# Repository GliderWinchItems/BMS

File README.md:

# BMS
Battery Management System

This repo has directories for three BMS designs.

The original plan used a LTC6813-1 (18 cells), but when it came time to order the pcb, the part was no longer available. The TI BQ76952 (16 cells) was then found to be available in a few months so that design was completed.
The testing of the first prototype with the BQA76952 turned up some unexplained failures, plus additional BQ76952 parts would not be available for approximately one year. 

The ADBMS1818 chip became available and samples were to be shipped in a few weeks, and additional parts available from Mouser in several months. This gave rise to the second design. The delivery schedule changed  and it would be about one year for samples and additional parts. This gave rise to a design based on the MAX14952.
The designs differ mainly in the BMS chip. The same processor, STM32L431RxT6, is used and the features are  nearly identical in the three designs, e.g. the trickle charger, CAN, and fan interfaces, etc. Much of the documentation for the BQ76952 board applies to all three designs.

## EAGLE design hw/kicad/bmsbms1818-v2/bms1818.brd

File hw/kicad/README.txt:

#README.txt
# 11/08/25

# Step 1: Convert eagle v4 format to v6.5
#
# The files in kicad are the result of loading the original eagle v4 files into
# eagle 6.5, then saving the .sch & .brd files.

# Step 2: Convert eagle 6.5 format to kicad.
#
# The eagle 6.5 files are imported into kicad and the resulting kicad format files are 
# saved.

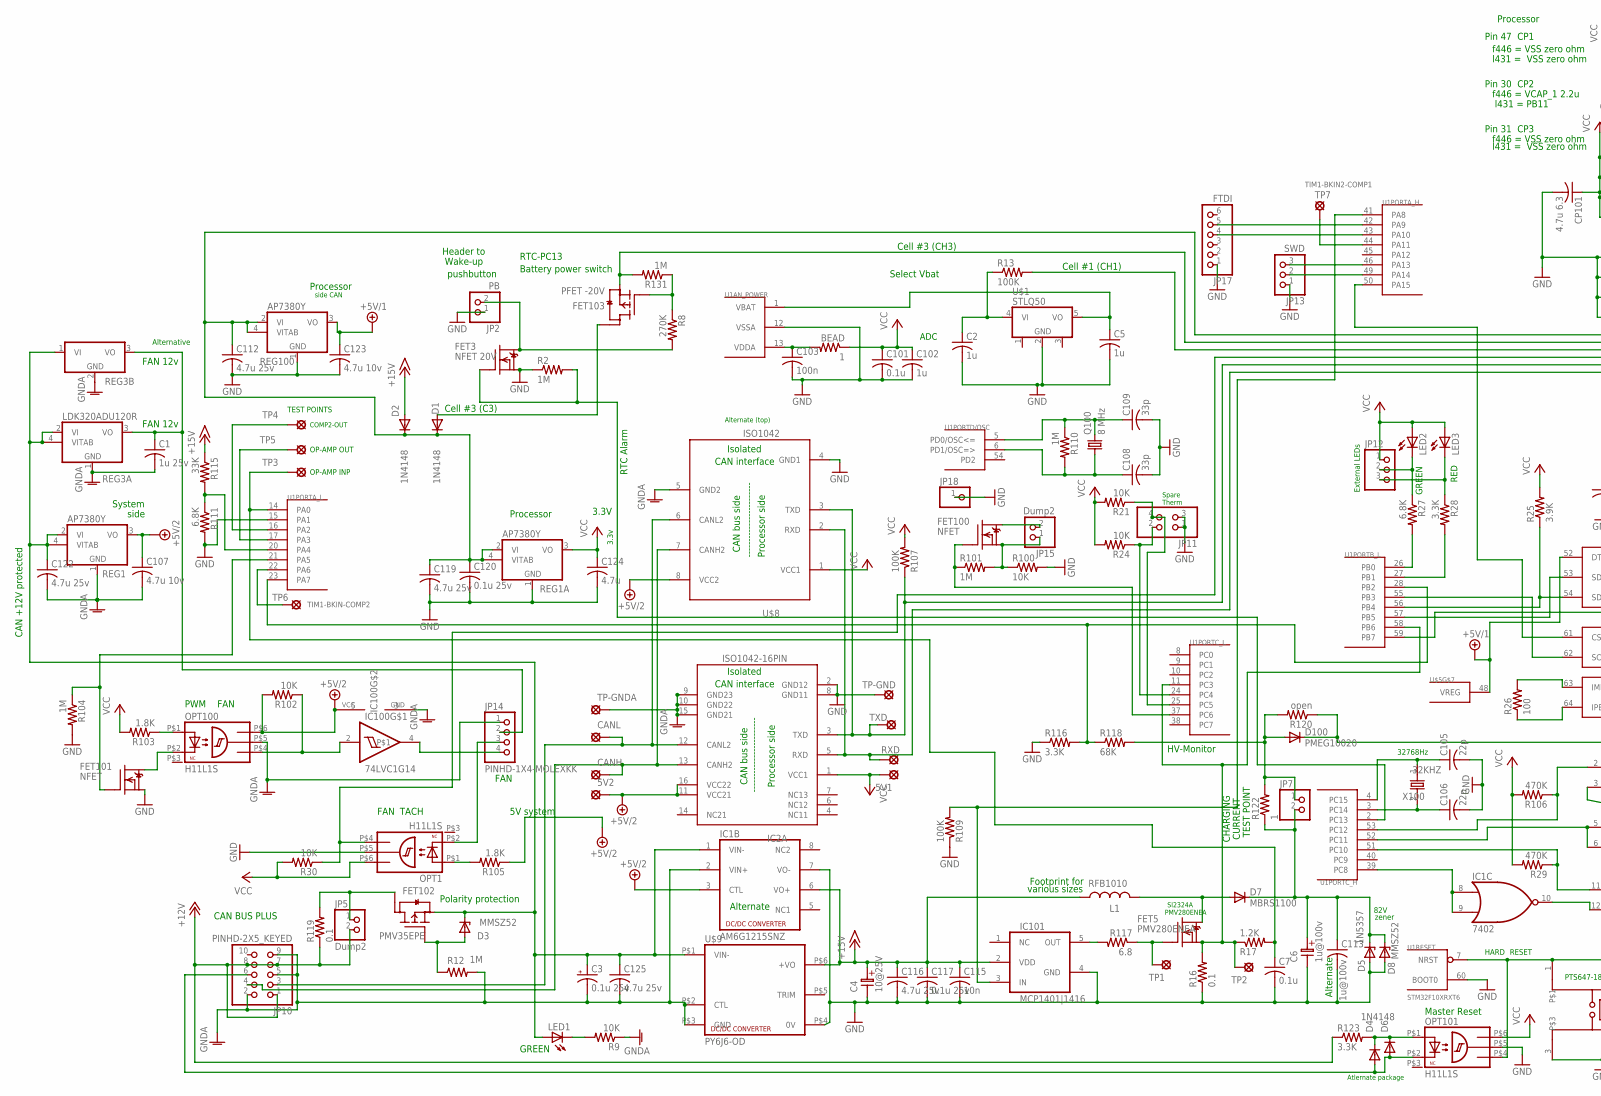
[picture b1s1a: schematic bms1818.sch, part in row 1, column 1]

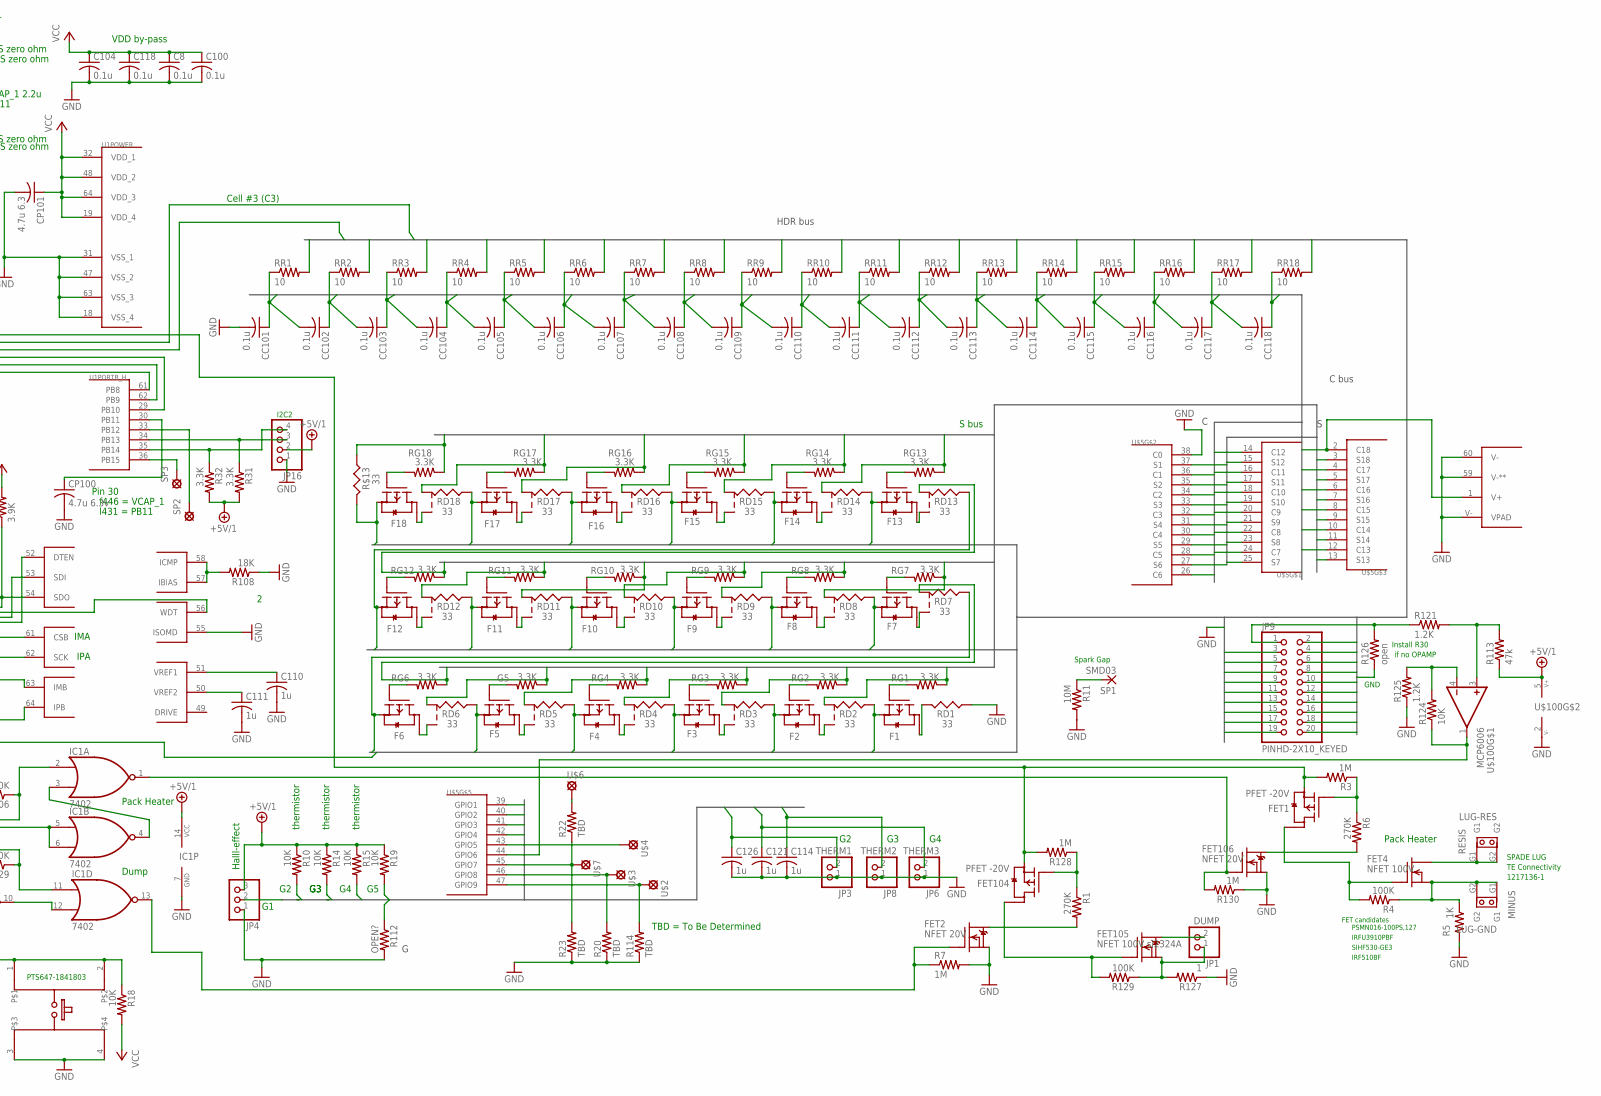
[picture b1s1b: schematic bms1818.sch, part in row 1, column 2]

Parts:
5V1, 5V2: SOLDPAD028; SOLPAD028
32KHZ: X100; 32KHZ
BEAD: 1; R0603
C1: 1u 25v; C0603
C2, C5, C102, C110, C111, C114, C121, C126: 1u; C0603
C3: 0.1u 25v; E5-8,5
C4: 10@25V; ES-2,5L
C6: 1u@100v; ES-2,5L
C7, C8, C100, C101, C104, C118: 0.1u; C0603
C103: 100n; C0603
C105, C106: 22p; C0603
C107, C123: 4.7u 10v; C0603
C108, C109: 33p; C0603
C112, C116, C119, C122, C125: 4.7u 25v; C0805
C113: 1u@100v; C1206
C115: 10n; C0603
C117, C120: 0.1u 25v; C0603
C124: 4.7u; C0603
CANH: SOLDPAD028; SOLPAD028
CANL: SOLDPAD028; SOLPAD028
CC101, CC102, CC103, CC104, CC105, CC106, CC107, CC108, CC109, CC110, CC111, CC112, CC113, CC114, CC115, CC116, CC117, CC118: 0.1u; C0603
CP100: 4.7u 6.3v; C0603
CP101: 4.7u 6.3; C0603
D1, D2: 1N4148; DO41-10_VERT
D3, D8: MMSZ52; SOD80C
D4: DIODE-SOD323-R; SOD323-R
D5: 1N5357; ZENER-VERT
D6: 1N4148; SOD123
D7: MBRS1100; SMB_1
D100: PMEG10020; SOD123W
F1, F2, F3, F4, F5, F6, F7, F8, F9, F10, F11, F12, F13, F14, F15, F16, F17, F18: FET-P-SOT23; SOT-23
FET1, FET103, FET104: PFET -20V; SOT-23
FET2, FET3, FET106: NFET 20V; SOT-23
FET4: NFET 100V; TO220V
FET5: PMV280ENEA; SOT-23
FET100, FET101: NFET; SOT-23
FET102: PMV35EPE; SOT-23
FET105: NFET 100V si2324A; SOT-23
G5: 3.3K; R0603
IC1: 7402; TSSOP14
IC1B: AM6G1215SNZ; DCDC7PINB
IC2A: ISO1042-16PIN; SO-16DW
IC100: 74LVC1G14; SOT-23
IC101: MCP1401|1416; SOT23-5
JP1: DUMP; 1X02
JP2: PB; 1X02
JP3: THERM1; 1X02
JP4, JP12: PINHD-1X3; 1X03
JP5, JP15: Dump2; 1X02
JP6: THERM3; 1X02
JP7: PINHD-1X2; 1X02
JP8: THERM2; 1X02
JP9: PINHD-2X10_KEYED; 2X10_KEYED
JP10: PINHD-2X5_KEYED; 2X05_KEYED
JP11: PINHD-2X2; 2X02
JP13: SWD; 1X03
JP14: PINHD-1X4-MOLEXKK; 1X4-MOLEXKK
JP16: PINHD-1X4; 1X04
JP17: FTDI; 1X06
JP18: PINHD-1X1; 1X01
L1: RFB1010; INDUCTOR6.0
LED1, LED2, LED3: LEDCHIP-LED0603; CHIP-LED0603
LUG-GND: MINUS; SPADE_TAB
LUG-RES: RESIS; SPADE_TAB
OPT1, OPT100, OPT101: H11L1S; SMD-6
Q100: 8 MHz; HC49/S
R1, R6, R8: 270K; R0603
R2, R3, R7, R12, R101, R104, R110, R128, R130, R131: 1M; R0603
R4, R13, R107, R109, R129: 100K; R0603
R5: 1K; R0603
R9, R10, R14, R15, R18, R19, R21, R24, R30, R100, R102, R124: 10K; R0603
R11: 10M; R0603
R16: 0.1; M1206
R17, R121, R125: 1.2K; R0603
R20, R22, R23, R114: TBD; R0603
R25: 3.9K; R0603
R26: 100; R0603
R27, R111: 6.8K; R0603
R28, R31, R32, R116, R123: 3.3K; R0603
R29, R106: 470K; R0603
R103, R105: 1.8K; R0603
R108: 18K; R0603
R112: OPEN?; R0603
R113: 47k; R0603
R115: 33K; R0603
R117: 6.8; R0603
R118: 68K; R0603
R119: 0.1; R0805
R120, R126: open; R0603
R122, R127: 1; R0603
R$13: 33; RS-2,5
RD1: 33; RS-2,5
RD2, RD3, RD4, RD5, RD6, RD7, RD8, RD9, RD10, RD11, RD12, RD13, RD14, RD15, RD16, RD17, RD18: 33; RS-2,5-2
REG1, REG1A, REG100: AP7380Y; SOT89
REG3A: LDK320ADU120R; SOT89
REG3B: LM7812T; TO220V
RESET: RESET; E-SWITCH2
RG1, RG2, RG3, RG4, RG6, RG7, RG8, RG9, RG10, RG11, RG12, RG13, RG14, RG15, RG16, RG17, RG18: 3.3K; R0603
RR1, RR2, RR3, RR4, RR5, RR6, RR7, RR8, RR9, RR10, RR11, RR12, RR13, RR14, RR15, RR16, RR17, RR18: 10; R0603
RXD: SOLDPAD028; SOLPAD028
SP1: SMD03
SP2, SP3: SOLDPAD028; SOLPAD028
TP1, TP2: SOLDPAD028; SOLPAD028
TP3, TP4, TP5, TP6, TP7: SOLDPAD0.6MM; SOLPAD.6MM
TP-GND: SOLDPAD028; SOLPAD028
TP-GNDA: SOLDPAD028; SOLPAD028
TXD: SOLDPAD028; SOLPAD028
U1: STM32F10XRXT6; TQFP64
U$1: STLQ50; SOT-323-5
U$2, U$3, U$4, U$6, U$7: SOLDPAD028; SOLPAD028
U$5: LTC6813; TQFP64_PAD
U$8: ISO1042; SOIC-8
U$9: PY6J6-OD; PYJ6-OD
U$100: MCP6006; SC-70-5

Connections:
12V-R: FET102.3 (D), JP5.1, R119.2
+5V/1: C123.1, IC1.14 (VCC), JP4.3, JP16.2, R10.1, R14.1, R15.1, R19.1, R31.2, R32.2, R113.1, REG100.3 (VO), U$5.48 (VREG), U$5.52 (DTEN), U$100.5 (V+)
+5V/2: 5V2.MP, C107.1, IC1B.3 (CTL), IC2A.11 (VCC21), IC2A.16 (VCC22), IC100.5 (VCC), OPT100.P$6 (VCC), R102.2, R105.1, REG1.3 (VO), U$8.8 (VCC2)
+12V: JP5.2, JP10.1, JP10.7, JP10.8, R119.1, R123.1
+15V: C4.1, C115.1, C116.1, C117.1, D2.A, IC1B.6 (VO+), IC101.2 (VDD), L1.1, R115.1, U$9.P$6 (+VO)
/PC10: IC1.3 (I1), IC1.4 (O)
BATSW-NDRAIN: FET3.3 (D), JP2.2, R8.2
BATSW-NDRAIN1: FET2.3 (D), R1.2
BATSW-NDRAIN2: FET106.3 (D), R6.2
BATSW-PGATE: FET103.1 (G), R8.1, R131.1
BATSW-PGATE1: FET104.1 (G), R1.1, R128.1
BATSW-PGATE2: FET1.1 (G), R3.1, R6.1
BIGFET-DRAIN: FET4.2 (D), LUG-RES.G1, LUG-RES.G2
BIGFET-GATE: FET1.3 (D), FET4.1 (G), R4.2
BIGFET-SOURCE: FET4.3 (S), LUG-GND.G1, LUG-GND.G2, R4.1, R5.1
C1: CC101.1, CC102.2, RR1.1, U$5.36 (C1)
C2: CC102.1, CC103.2, RR2.1, U$5.34 (C2)
C3: CC103.1, CC104.2, RR3.1, U$5.32 (C3)
C4: CC104.1, CC105.2, RR4.1, U$5.30 (C4)
C5: CC105.1, CC106.2, RR5.1, U$5.28 (C5)
C6: CC106.1, CC107.2, RR6.1, U$5.26 (C6)
C7: CC107.1, CC108.2, RR7.1, U$5.24 (C7)
C8: CC108.1, CC109.2, RR8.1, U$5.22 (C8)
C9: CC109.1, CC110.2, RR9.1, U$5.20 (C9)
C10: CC110.1, CC111.2, RR10.1, U$5.18 (C10)
C11: CC111.1, CC112.2, RR11.1, U$5.16 (C11)
C12: CC112.1, CC113.2, RR12.1, U$5.14 (C12)
C13: CC113.1, CC114.2, RR13.1, U$5.12 (C13)
C14: CC114.1, CC115.2, RR14.1, U$5.10 (C14)
C15: CC115.1, CC116.2, RR15.1, U$5.8 (C15)
C16: CC116.1, CC117.2, RR16.1, U$5.6 (C16)
C17: CC117.1, CC118.2, RR17.1, U$5.4 (C17)
C18: CC118.1, RR18.1, U$5.1 (V+), U$5.2 (C18)
CAN+12PRO: C3.+, C122.1, C125.1, D3.C, FET102.2 (S), IC1B.1 (VIN-), LED1.A, REG1.2 (VI), REG1.4 (VITAB), REG3A.2 (VI), REG3A.4 (VITAB), REG3B.1 (VI), U$9.P$1 (VIN-)
CANH2: CANH.MP, IC2A.13 (CANH2), JP10.4, U$8.7 (CANH2)
CANL2: CANL.MP, IC2A.12 (CANL2), JP10.3, U$8.6 (CANL2)
CELL1-PFET-DRAIN: D1.A, FET103.3 (D)
CH1: F1.2 (S), JP9.12, R13.2, RD2.1, RR1.2
CH2: F2.2 (S), JP9.3, RD3.1, RR2.2
CH3: F3.2 (S), FET103.2 (S), JP9.13, R131.2, RD4.1, RR3.2
CH4: F4.2 (S), JP9.4, RD5.1, RR4.2
CH5: F5.2 (S), JP9.14, RD6.1, RR5.2
CH6: F6.2 (S), JP9.5, RD7.1, RR6.2
CH7: F7.2 (S), JP9.15, RD8.1, RR7.2
CH8: F8.2 (S), JP9.6, RD9.1, RR8.2
CH9: F9.2 (S), JP9.16, RD10.1, RR9.2
CH10: F10.2 (S), JP9.7, RD11.1, RR10.2
CH11: F11.2 (S), JP9.17, RD12.1, RR11.2
CH12: F12.2 (S), JP9.8, RD13.1, RR12.2
CH13: F13.2 (S), JP9.18, RD14.1, RR13.2
CH14: F14.2 (S), JP9.9, RD15.1, RR14.2
CH15: F15.2 (S), JP9.19, RD16.1, RR15.2
CH16: F16.2 (S), JP9.10, RD17.1, RR16.2
CH17: F17.2 (S), JP9.20, RD18.1, RR17.2
CH18: D100.A (C), F18.2 (S), JP9.11, R120.1, R$13.2, RR18.2
CHGR-FET-DRAIN: D7.A, FET5.3 (D), L1.2
CHGR-TEST-V+: D100.C (A), JP7.1, R118.2, R120.2, R122.2
CHGR-V+: C6.1, C113.1, D5.2 (C), D7.C, D8.C, JP7.2, R122.1
DRAIN$1: F1.3 (D), RD1.2
DRAIN$2: F2.3 (D), RD2.3
DRAIN$3: F3.3 (D), RD3.3
DRAIN$4: F4.3 (D), RD4.3
DRAIN$5: F5.3 (D), RD5.3
DRAIN$6: F6.3 (D), RD6.3
DRAIN$7: F7.3 (D), RD7.3
DRAIN$8: F8.3 (D), RD8.3
DRAIN$9: F9.3 (D), RD9.3
DRAIN$10: F10.3 (D), RD10.3
DRAIN$11: F11.3 (D), RD11.3
DRAIN$12: F12.3 (D), RD12.3
DRAIN$13: F13.3 (D), RD13.3
DRAIN$14: F14.3 (D), RD14.3
DRAIN$15: F15.3 (D), RD15.3
DRAIN$16: F16.3 (D), RD16.3
DRAIN$17: F17.3 (D), RD17.3
DRAIN$18: F18.3 (D), RD18.3
DUMP2: FET100.3 (D), JP15.2
DUMP2FET-SOURCE: FET100.2 (S), JP15.1, R100.1, R101.2
DUMPFET-DRAIN: FET105.3 (D), JP1.2
DUMPFET-GATE: FET104.3 (D), FET105.1 (G), R129.2
DUMPFET-SOURCE: FET105.2 (S), JP1.1, R127.2, R129.1
FAN+12: C1.1, JP14.2, REG3A.3 (VO), REG3B.3 (VO)
FANPWN: IC100.2 (I), OPT100.P$4 (OUT), R102.1
FANPWN-INVERT: IC100.4, JP14.4
FANTACH-H11DIODE: JP14.3, OPT1.P$2 (C)
FANTACH-RESISTOR: OPT1.P$1 (A), R105.2
FET103-GATE: D3.A, FET102.1 (G), R12.1
G1: JP4.2, U$5.39 (GPIO1)
G2: C126.1, JP3.2, R10.2, U$5.40 (GPIO2)
G3: C121.1, JP6.2, R14.2, U$5.41 (GPIO3)
G4: C114.1, JP8.2, R15.2, U$5.42 (GPIO4)
G5: R19.2, R112.1, U$4.MP, U$5.43 (GPIO5)
G6: R124.1, U$5.44 (GPIO6), U$100.1 (OUT)
G7: R22.1, R23.2, U$5.45 (GPIO7), U$7.MP
G7-DIVIDER-HIGH: R22.2, U$6.MP
G8: R20.2, U$3.MP, U$5.46 (GPIO8)
G9: R114.2, U$2.MP, U$5.47 (GPIO9)
GATE-DRV-MCP1416: IC101.5 (OUT), R117.2
GHR_FET_GATE: FET5.1 (G), R117.1, TP1.MP
GND: C2.2, C4.2, C5.2, C6.2, C7.2, C8.2, C100.2, C101.2, C102.2, C103.2, C104.2, C105.2, C106.2, C108.2, C109.2, C110.2, C111.2, C112.2, C113.2, C114.2, C115.2, C116.2, C117.2, C118.2, C119.2, C120.2, C121.2, C123.2, C124.2, C126.2, CC101.2, CP100.2, CP101.2, D5.1 (A), D8.A, FET2.2 (S), FET3.2 (S), FET101.2 (S), FET106.2 (S), IC1.7 (GND), IC1B.7 (VO-), IC2A.2 (GND12), IC2A.8 (GND11), IC101.4 (GND), JP2.1, JP3.1, JP4.1, JP6.1, JP8.1, JP9.2, JP11.1, JP11.3, JP13.1, JP16.1, JP17.1, JP18.1, OPT1.P$5 (GND), OPT101.P$5 (GND), R2.1, R5.2, R7.2, R11.2, R16.1, R20.1, R23.1, R100.2, R104.2, R108.1, R109.1, R111.2, R112.2, R114.1, R116.1, R125.1, R126.1, R127.1, R130.1, RD1.1, REG1A.1 (GND), REG100.1 (GND)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
GNDA: C1.2, C3.-, C107.2, C122.2, C125.2, IC1B.2 (VIN+), IC2A.9 (GND23), IC2A.10 (GND22), IC2A.15 (GND21), IC100.3 (GND), JP10.2, JP10.5, JP10.9, JP14.1, OPT100.P$5 (GND), R9.1, R12.2, REG1.1 (GND), REG3A.1 (GND), REG3B.2 (GND), TP-GNDA.MP, U$8.5 (GND2), U$9.P$2 (CTL), U$9.P$3 (GND)
GT1: F1.1 (G), RG1.2
GT2: F2.1 (G), RG2.2
GT3: F3.1 (G), RG3.2
GT4: F4.1 (G), RG4.2
GT5: F5.1 (G), G5.2
GT6: F6.1 (G), RG6.2
GT7: F7.1 (G), RG7.2
GT8: F8.1 (G), RG8.2
GT9: F9.1 (G), RG9.2
GT10: F10.1 (G), RG10.2
GT11: F11.1 (G), RG11.2
GT12: F12.1 (G), RG12.2
GT13: F13.1 (G), RG13.2
GT14: F14.1 (G), RG14.2
GT15: F15.1 (G), RG15.2
GT16: F16.1 (G), RG16.2
GT17: F17.1 (G), RG17.2
GT18: F18.1 (G), RG18.2
H11L-PWM-R: OPT100.P$1 (A), R103.1
H11PWM-FETDRV: FET101.3 (D), OPT100.P$2 (C)
ICMP-IBIAS: R108.2, U$5.57 (IBIAS), U$5.58 (ICMP)
IMB: R26.2, U$5.63 (IMB)
IPB: R26.1, U$5.64 (IPB)
K1: R11.1, SP1.1
LED-EXT-GRN-CATHODE: JP12.2, LED2.C, R27.1
LED-EXT-RED-CATHODE: JP12.3, LED3.C, R28.1
LED_BUS_PWR: LED1.C, R9.2
MASTER-RESET-RESISTOR: D4.C, D6.C, OPT101.P$1 (A), R123.2
MASTER-RESET-SYS: D4.A, D6.A, JP10.6, OPT101.P$2 (C)
unnamed: JP9.1, R121.1, R126.2
NRST: OPT101.P$4 (OUT), R18.1, RESET.1, RESET.2, U1.7 (NRST)
OPA-VIN+: R113.2, R121.2, U$100.3 (+IN)
OPA-VIN-: R124.2, R125.2, U$100.4 (-IN)
PA0-OP-FILTERCURRENT: C7.1, R17.2, TP3.MP, U1.14 (PA0)
PA2-COMP2-OUT: TP4.MP, U1.16 (PA2)
PA3-OPAMP_INP: TP5.MP, U1.17 (PA3)
PA4-15V-OR-DIVIDED-IN4: R111.1, R115.2, U1.20 (PA4)
PA5-FETGATE-FAN-PWM: FET101.1 (G), R104.1, U1.21 (PA5)
PA6-T1-BKIN-COMP2: TP6.MP, U1.22 (PA6)
PA8-T1C1-MCP1416_DRV: IC101.3 (IN), R109.2, U1.41 (PA8)
PA9-USART1-TX: JP17.5, U1.42 (PA9)
PA10-USART1-RX: JP17.4, U1.43 (PA10)
PA13-SWDIO: JP13.3, U1.46 (PA13)
PA14-SWCLK: JP13.2, U1.49 (PA14)
PA15-SP1_NSS-CSB: U1.50 (PA15), U$5.61 (CSB)
PB0-LED-GRN: R27.2, U1.26 (PB0)
PB1-LED-RED: R28.2, U1.27 (PB1)
PB2-PA7-HV-DIV-COMP1_INP: R116.2, R118.1, U1.23 (PA7), U1.28 (PB2)
PB3-SPI1_SCK-SCK: U1.55 (PB3), U$5.62 (SCK)
PB4-SP1_MISO-SDO: R25.1, U1.56 (PB4), U$5.54 (SDO)
PB5-SPI1_MOSI-SDI: U1.57 (PB5), U$5.53 (SDI)
PB6-PC3-COMP2_INP-CURRENT-SENSE: FET5.2 (S), R16.2, R17.1, TP2.MP, U1.11 (PC3), U1.58 (PB6)
PB7|WDT: U1.59 (PB7), U$5.56 (WDT)
PB8-CAN-RX: IC2A.5 (RXD), RXD.MP, U1.61 (PB8), U$8.2 (RXD)
PB9-CAN-TX: IC2A.3 (TXD), R107.1, TXD.MP, U1.62 (PB9), U$8.3 (TXD)
PB10-T2C3-FANTACH-H11L1OUT: OPT1.P$4 (OUT), R30.1, U1.29 (PB10)
PB11-I2C2-SDA|VCAP1: CP100.1, U1.30 (PB11)
PB12-SPI2-NSS: SP2.MP, U1.33 (PB12)
PB14-I2C2-SDA: JP16.4, R32.1, U1.35 (PB14)
PB-13-I2C2-SCK: JP16.3, R31.1, U1.34 (PB13)
PB-15: SP3.MP, U1.36 (PB15)
PC4: JP11.2, R24.1, U1.24 (PC4)
PC5: JP11.4, R21.1, U1.25 (PC5)
PC6-DUMPFET-GATE: FET100.1 (G), R101.1, U1.37 (PC6)
PC8-/DUMP: IC1.8 (I0), IC1.9 (I1), U1.39 (PC8)
PC8-DUMP: IC1.10 (O), IC1.12 (I1)
PC10&/PC8-DUMP-FET-GATE: FET2.1 (G), IC1.13 (O), R7.1
PC10-DUMP: IC1.11 (I0), R29.1, U1.51 (PC10)
PC11-/HEATER: IC1.5 (I0), IC1.6 (I1), U1.52 (PC11)
PC12-HEATER: IC1.2 (I0), R106.1, U1.53 (PC12)
PC13-RTC-OUT: FET3.1 (G), R2.2, U1.2 (PC13)
PC14_OSC32IN|XTAL: 32KHZ.2, C106.1, U1.3 (PC14)
PC15-32OSC-OUT: 32KHZ.1, C105.1, U1.4 (PC15)
PD0_OSC_IN_XTAL: C109.1, Q100.2, R110.1, U1.5 (PD0/OSC<=)
PD1_OSC_OUT: C108.1, Q100.1, R110.2, U1.6 (PD1/OSC=>)
S1: RD2.2, RG1.1, U$5.37 (S1)
S2: RD3.2, RG2.1, U$5.35 (S2)
S3: RD4.2, RG3.1, U$5.33 (S3)
S4: RD5.2, RG4.1, U$5.31 (S4)
S5: G5.1, RD6.2, U$5.29 (S5)
S6: RD7.2, RG6.1, U$5.27 (S6)
S7: RD8.2, RG7.1, U$5.25 (S7)
S8: RD9.2, RG8.1, U$5.23 (S8)
S9: RD10.2, RG9.1, U$5.21 (S9)
S10: RD11.2, RG10.1, U$5.19 (S10)
S11: RD12.2, RG11.1, U$5.17 (S11)
S12: RD13.2, RG12.1, U$5.15 (S12)
S13: RD14.2, RG13.1, U$5.13 (S13)
S14: RD15.2, RG14.1, U$5.11 (S14)
S15: RD16.2, RG15.1, U$5.9 (S15)
S16: RD17.2, RG16.1, U$5.7 (S16)
S17: RD18.2, RG17.1, U$5.5 (S17)
S18: R$13.1, RG18.1, U$5.3 (S18)
TIM1_BKIN2_COMP2: TP7.MP, U1.44 (PA11)
V-ORED: C112.1, C119.1, C120.1, D1.C, D2.C, FET1.2 (S), FET104.2 (S), R3.2, R128.2, REG1A.2 (VI), REG1A.4 (VITAB), REG100.2 (VI), REG100.4 (VITAB)
VBAT-REG-IN: C2.1, R13.1, U$1.4 (VI)
VBAT-REG-OUT: C5.1, U1.1 (VBAT), U$1.5 (VO)
VCC: 5V1.MP, BEAD.1, C8.1, C100.1, C101.1, C102.1, C104.1, C118.1, C124.1, CP101.1, IC2A.1 (VCC1), JP12.1, LED2.A, LED3.A, OPT1.P$6 (VCC), OPT101.P$6 (VCC), R18.2, R21.2, R24.2, R25.2, R29.2, R30.2, R103.2, R106.2, R107.2, REG1A.3 (VO), U1.19 (VDD_4), U1.32 (VDD_1), U1.48 (VDD_2), U1.64 (VDD_3), U$8.1 (VCC1)
VDDA1: BEAD.2, C103.1, U1.13 (VDDA)
VREF3: C110.1, U$5.51 (VREF1)
VREF4: C111.1, U$5.50 (VREF2)
XOR-BIGFET-GATE: FET106.1 (G), IC1.1 (O), R130.2

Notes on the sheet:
CAN interface
CAN bus side
CAN BUS PLUS
------------------------
FAN
82V
TACH
PWM
5V system
Master Reset
Alternate
TEST POINT
CURRENT
CHARGING
RESET
HARD
3.3V
Wake-up
pushbutton
Battery power
switch
Pin 47
Pin 30
f446 = VCAP_1 2.2u
Pin 31
f446 = VSS zero ohm
CP1
CP3
f446 = VCAP_1
CP2
ADC
32768Hz
RTC Alarm
GREEN
RED
3.3v
Cell #3 (C3)
Pack Heater
1217136-1
TE Connectivity

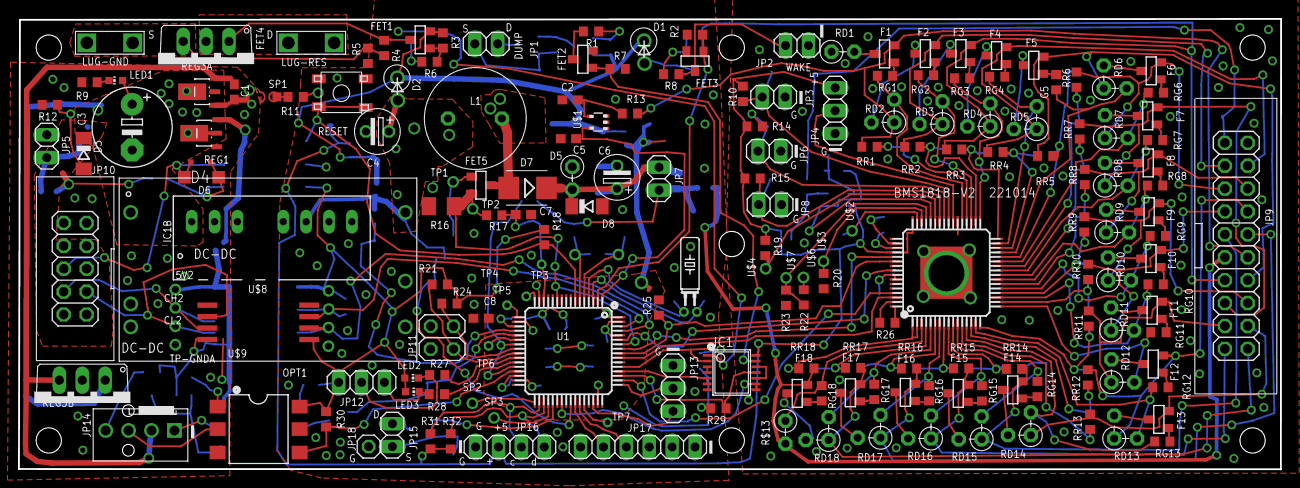
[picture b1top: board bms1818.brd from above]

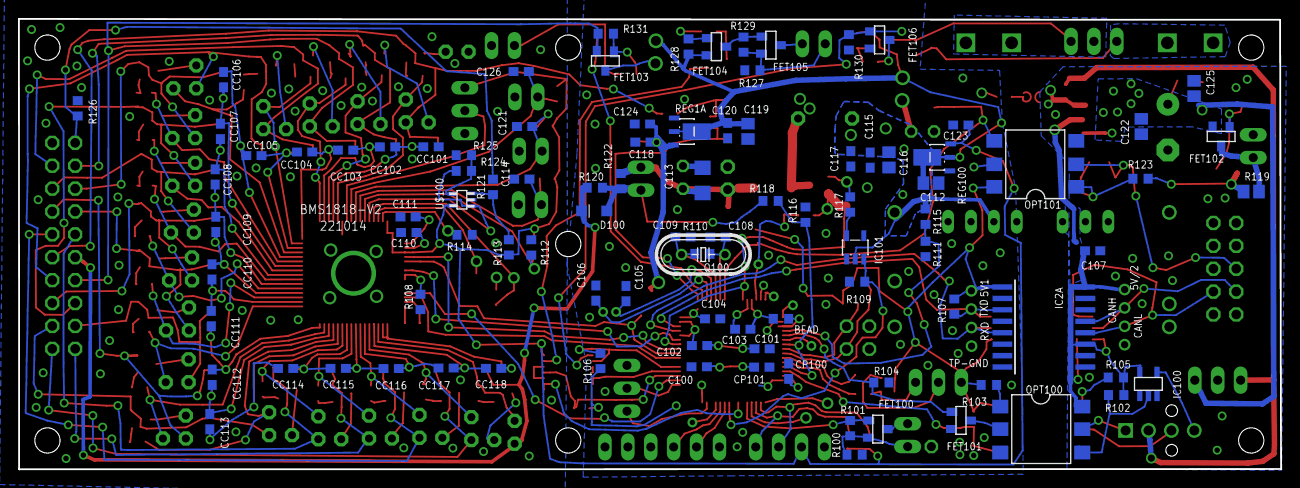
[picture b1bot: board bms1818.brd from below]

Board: 2 copper layers, 140.1 x 50.0 mm, 283 parts (97 on the bottom side), 203 nets.

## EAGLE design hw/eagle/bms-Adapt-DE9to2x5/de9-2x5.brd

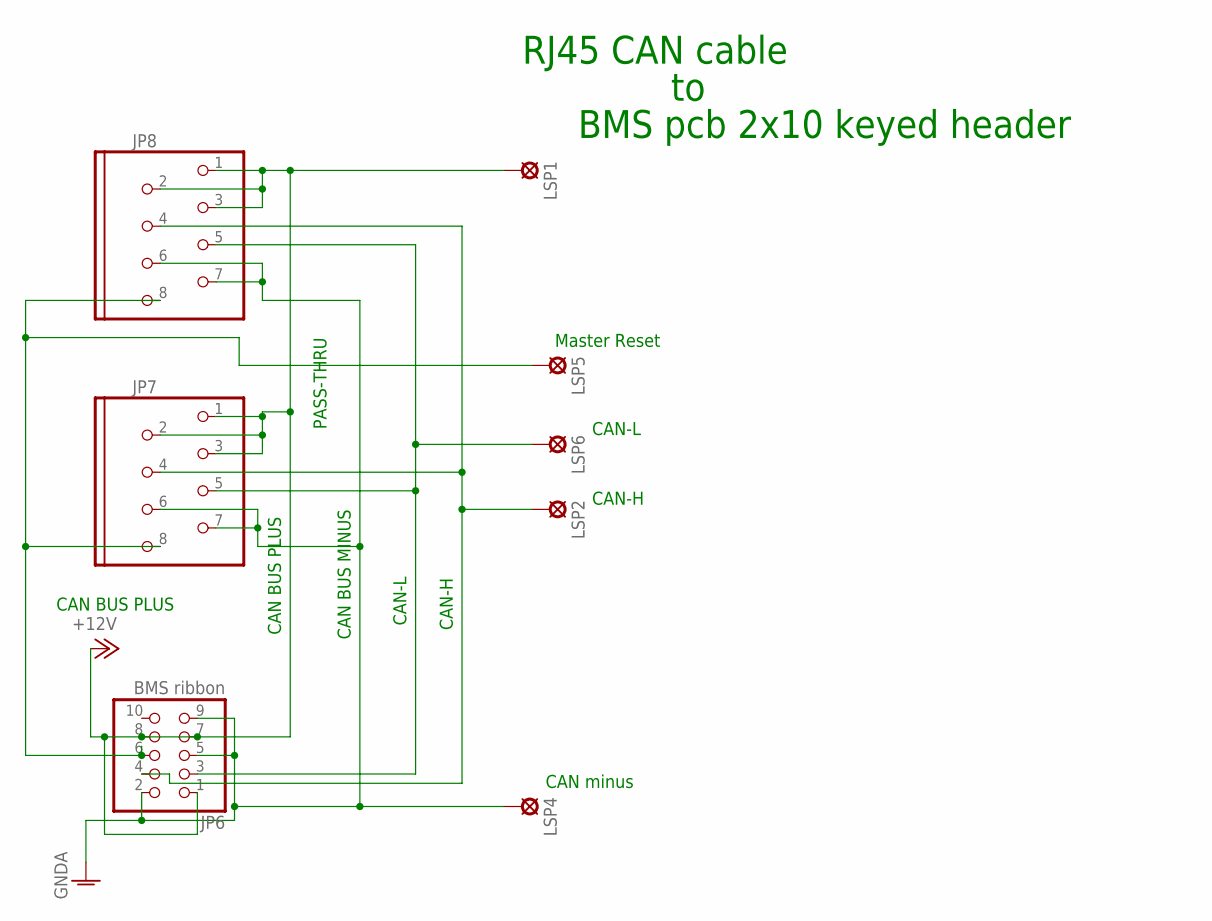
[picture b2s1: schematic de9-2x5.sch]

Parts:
JP6: BMS ribbon; 2X05_KEYED
JP7, JP8: MOD8P8C
LSP1, LSP4: SE14
LSP2, LSP5, LSP6: LSP10

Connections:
+12V: JP6.1, JP6.7, JP6.8, JP7.1, JP7.2 (5), JP7.3 (2), JP8.1, JP8.2 (5), JP8.3 (2), LSP1.MP
CANH: JP6.4, JP7.4 (6), JP8.4 (6), LSP2.MP
CANL: JP6.3, JP7.5 (3), JP8.5 (3), LSP6.MP
GNDA: JP6.2, JP6.5, JP6.9, JP7.6 (7), JP7.7 (4), JP8.6 (7), JP8.7 (4), LSP4.MP
MASTER-RESET-SYS: JP6.6, JP7.8, JP8.8, LSP5.MP

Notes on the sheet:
CAN BUS PLUS
PASS-THRU
CAN BUS MINUS
CAN-H
CAN-L
RJ45 CAN cable
BMS pcb 2x10 keyed header
Master Reset
CAN minus

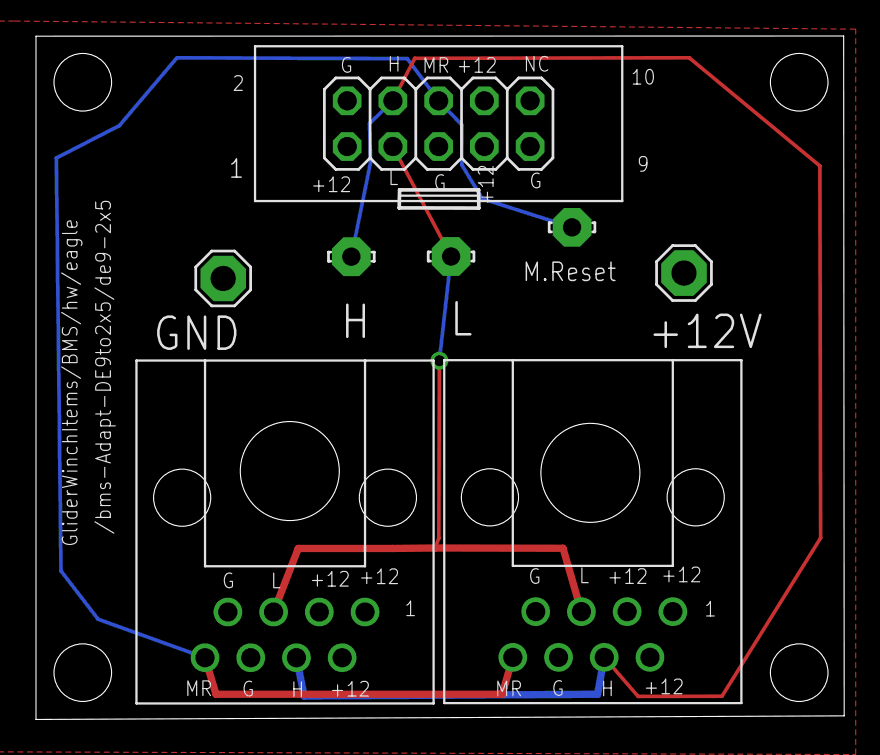
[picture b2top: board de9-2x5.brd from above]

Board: 2 copper layers, 44.9 x 38.0 mm, 8 parts (0 on the bottom side), 5 nets.

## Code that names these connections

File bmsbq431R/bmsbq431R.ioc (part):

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Mcu.Name=STM32L431R(B-C)Tx
Mcu.Package=LQFP64
Mcu.UserName=STM32L431RBTx
PA0.GPIOParameters=GPIO_Label
PA0.GPIO_Label=OPAMP-INP
PA0.Signal=SharedAnalog_PA0
PA1.GPIOParameters=GPIO_Label
PA1.GPIO_Label=OPAMP-INM
PA1.Signal=SharedAnalog_PA1
PA10.Mode=Asynchronous
PA10.Signal=USART1_RX
PA11.Mode=ExternalOutput_TIM1BKIN2
PA11.Signal=TIM1_BKIN2_COMP1
PA13\ (JTMS-SWDIO).Mode=Serial_Wire
PA13\ (JTMS-SWDIO).Signal=SYS_JTMS-SWDIO
PA14\ (JTCK-SWCLK).Mode=Serial_Wire
PA14\ (JTCK-SWCLK).Signal=SYS_JTCK-SWCLK
PA2.Mode=ExternalOutput
PA2.Signal=COMP2_OUT
PA3.GPIOParameters=GPIO_Label
PA3.GPIO_Label=OPAMP_OUT
PA3.Signal=SharedAnalog_PA3
PA4.GPIOParameters=GPIO_Label
PA4.GPIO_Label=dc-dc-15V
PA4.Signal=SharedAnalog_PA4
PA5.Signal=S_TIM2_CH1
PA6.Mode=ExternalOutput_TIM1BKIN
PA6.Signal=TIM1_BKIN_COMP2
PA7.GPIOParameters=GPIO_Label
PA7.GPIO_Label=HV-div1
PA7.Signal=SharedAnalog_PA7
PA8.Signal=S_TIM1_CH1
PA9.Mode=Asynchronous
PA9.Signal=USART1_TX
PB0.GPIOParameters=PinState,GPIO_Label
PB0.GPIO_Label=LED_RED
PB0.PinState=GPIO_PIN_SET
PB0.Signal=GPIO_Output
PB1.GPIOParameters=PinState,GPIO_Label
PB1.GPIO_Label=LED_GRN
PB1.PinState=GPIO_PIN_SET
PB1.Signal=GPIO_Output
PB10.GPIOParameters=GPIO_PuPd,GPIO_Label
PB10.GPIO_Label=FAN-TACH
PB10.GPIO_PuPd=GPIO_PULLUP
PB10.Signal=S_TIM2_CH3
PB12.GPIOParameters=GPIO_Label
PB12.GPIO_Label=PADxx
PB12.Signal=GPIO_Output
PB13.GPIOParameters=GPIO_Speed,GPIO_Pu
PB13.GPIO_Pu=GPIO_NOPULL
PB13.GPIO_Speed=GPIO_SPEED_FREQ_LOW
PB13.Signal=I2C2_SCL
PB14.GPIOParameters=GPIO_Pu
PB14.GPIO_Pu=GPIO_NOPULL
PB14.Signal=I2C2_SDA
PB15.GPIOParameters=GPIO_Label
PB15.GPIO_Label=PAD7
PB15.Signal=GPIO_Output
PB2.GPIOParameters=GPIO_Label
PB2.GPIO_Label=HV-div2
PB2.Signal=SharedAnalog_PB2
PB3\ (JTDO-TRACESWO).GPIOParameters=GPIO_Label
PB3\ (JTDO-TRACESWO).GPIO_Label=ALERT
PB3\ (JTDO-TRACESWO).Signal=GPXTI3
PB4\ (NJTRST).GPIOParameters=GPIO_Label
PB4\ (NJTRST).GPIO_Label=FET-CUR-A1
PB4\ (NJTRST).Signal=SharedAnalog_PB4
PB5.GPIOParameters=GPIO_Label
PB5.GPIO_Label=BQ-RST-SHUT
PB5.Signal=GPIO_Output
PB6.GPIOParameters=GPIO_Label,GPIO_Pu
PB6.GPIO_Label=BQ-SCL
PB6.GPIO_Pu=GPIO_PULLUP
PB6.Mode=I2C
PB6.Signal=I2C1_SCL
PB7.GPIOParameters=GPIO_Label,GPIO_Pu
PB7.GPIO_Label=BQ-SDA
PB7.GPIO_Pu=GPIO_PULLUP
PB7.Mode=I2C
PB7.Signal=I2C1_SDA
PB8.Mode=CAN_Activate
PB8.Signal=CAN1_RX
PB9.Mode=CAN_Activate
PB9.Signal=CAN1_TX
PC1.GPIOParameters=GPIO_Label
PC1.GPIO_Label=FET-CUR-RC
PC1.Signal=SharedAnalog_PC1
PC10.GPIOParameters=GPIO_Label
PC10.GPIO_Label=DUMP
PC10.Signal=GPIO_Output
PC11.GPIOParameters=GPIO_Label
PC11.GPIO_Label=HEATER_NOT
PC11.Signal=GPIO_Output
PC12.GPIOParameters=GPIO_Label
PC12.GPIO_Label=HEATER
PC12.Signal=GPIO_Output
PC13.Mode=AlarmA_RoutedAF
PC13.Signal=RTC_OUT_ALARM
PC3.GPIOParameters=GPIO_Label
PC3.GPIO_Label=FET_CUR-A2
PC3.Signal=SharedAnalog_PC3
PC4.GPIOParameters=GPIO_Label
PC4.GPIO_Label=Therm-spare1
PC4.Signal=ADCx_IN13
PC5.GPIOParameters=GPIO_Label
PC5.GPIO_Label=Therm-spare2
PC5.Signal=ADCx_IN14
PC6.GPIOParameters=GPIO_PuPd,GPIO_Label
PC6.GPIO_Label=DUMP2
PC6.GPIO_PuPd=GPIO_PULLDOWN
PC6.Signal=GPIO_Output
PC8.GPIOParameters=GPIO_Label
PC8.GPIO_Label=DUMP_NOT
PC8.Signal=GPIO_Output
PD2.GPIOParameters=GPIO_Label
PD2.GPIO_Label=BQ_LD
PD2.Signal=GPIO_Output
PH0-OSC_IN\ (PH0).Mode=HSE-External-Oscillator
PH0-OSC_IN\ (PH0).Signal=RCC_OSC_IN
PH1-OSC_OUT\ (PH1).Mode=HSE-External-Oscillator
PH1-OSC_OUT\ (PH1).Signal=RCC_OSC_OUT
RCC.HSE_VALUE=8000000
RCC.SYSCLKFreq_VALUE=16000000
RCC.SYSCLKSource=RCC_SYSCLKSOURCE_PLLCLK
board=custom

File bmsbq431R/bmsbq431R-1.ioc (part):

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Mcu.Name=STM32L431R(B-C)Tx
Mcu.Package=LQFP64
Mcu.UserName=STM32L431RBTx
PA0.GPIOParameters=GPIO_Label
PA0.GPIO_Label=OPAMP-INP
PA0.Signal=SharedAnalog_PA0
PA1.GPIOParameters=GPIO_Label
PA1.GPIO_Label=OPAMP-INM
PA1.Signal=SharedAnalog_PA1
PA10.Mode=Asynchronous
PA10.Signal=USART1_RX
PA11.Mode=ExternalOutput_TIM1BKIN2
PA11.Signal=TIM1_BKIN2_COMP1
PA13\ (JTMS-SWDIO).Mode=Serial_Wire
PA13\ (JTMS-SWDIO).Signal=SYS_JTMS-SWDIO
PA14\ (JTCK-SWCLK).Mode=Serial_Wire
PA14\ (JTCK-SWCLK).Signal=SYS_JTCK-SWCLK
PA2.Mode=ExternalOutput
PA2.Signal=COMP2_OUT
PA3.GPIOParameters=GPIO_Label
PA3.GPIO_Label=OPAMP_OUT
PA3.Signal=SharedAnalog_PA3
PA4.GPIOParameters=GPIO_Label
PA4.GPIO_Label=dc-dc-15V
PA4.Signal=SharedAnalog_PA4
PA5.GPIOParameters=GPIO_Label
PA5.GPIO_Label=FAN-PWM
PA5.Signal=S_TIM2_CH1
PA6.Mode=ExternalOutput_TIM1BKIN
PA6.Signal=TIM1_BKIN_COMP2
PA7.GPIOParameters=GPIO_Label
PA7.GPIO_Label=HV-div1
PA7.Signal=SharedAnalog_PA7
PA8.Signal=S_TIM1_CH1
PA9.Mode=Asynchronous
PA9.Signal=USART1_TX
PB0.GPIOParameters=PinState,GPIO_Label
PB0.GPIO_Label=LED_RED
PB0.PinState=GPIO_PIN_SET
PB0.Signal=GPIO_Output
PB1.GPIOParameters=PinState,GPIO_Label
PB1.GPIO_Label=LED_GRN
PB1.PinState=GPIO_PIN_SET
PB1.Signal=GPIO_Output
PB10.GPIOParameters=GPIO_PuPd,GPIO_Label
PB10.GPIO_Label=FAN-TACH
PB10.GPIO_PuPd=GPIO_PULLUP
PB10.Signal=S_TIM2_CH3
PB12.GPIOParameters=GPIO_Label
PB12.GPIO_Label=PADxx
PB12.Signal=GPIO_Output
PB13.GPIOParameters=GPIO_Speed,GPIO_PuPdOD
PB13.GPIO_PuPdOD=GPIO_NOPULL
PB13.GPIO_Speed=GPIO_SPEED_FREQ_LOW
PB13.Mode=I2C
PB13.Signal=I2C2_SCL
PB14.GPIOParameters=GPIO_PuPdOD
PB14.GPIO_PuPdOD=GPIO_NOPULL
PB14.Mode=I2C
PB14.Signal=I2C2_SDA
PB15.GPIOParameters=GPIO_Label
PB15.GPIO_Label=PAD7
PB15.Signal=GPIO_Output
PB2.GPIOParameters=GPIO_Label
PB2.GPIO_Label=HV-div2
PB2.Signal=SharedAnalog_PB2
PB3\ (JTDO-TRACESWO).GPIOParameters=GPIO_PuPd,GPIO_Label
PB3\ (JTDO-TRACESWO).GPIO_Label=BQ-ALERT
PB3\ (JTDO-TRACESWO).GPIO_PuPd=GPIO_PULLUP
PB3\ (JTDO-TRACESWO).Signal=GPIO_Input
PB4\ (NJTRST).GPIOParameters=GPIO_Label
PB4\ (NJTRST).GPIO_Label=FET-CUR-A1
PB4\ (NJTRST).Signal=SharedAnalog_PB4
PB5.GPIOParameters=GPIO_Label
PB5.GPIO_Label=BQ-RST-SHUT
PB5.Signal=GPIO_Output
PB6.GPIOParameters=GPIO_Label
PB6.GPIO_Label=BQ-SCL
PB6.Mode=I2C
PB6.Signal=I2C1_SCL
PB7.GPIOParameters=GPIO_Label
PB7.GPIO_Label=BQ-SDA
PB7.Mode=I2C
PB7.Signal=I2C1_SDA
PB8.Mode=CAN_Activate
PB8.Signal=CAN1_RX
PB9.Mode=CAN_Activate
PB9.Signal=CAN1_TX
PC1.GPIOParameters=GPIO_Label
PC1.GPIO_Label=FET-CUR-RC
PC1.Signal=SharedAnalog_PC1
PC10.GPIOParameters=GPIO_Label
PC10.GPIO_Label=DUMP
PC10.Signal=GPIO_Output
PC11.GPIOParameters=GPIO_Label
PC11.GPIO_Label=HEATER_NOT
PC11.Signal=GPIO_Output
PC12.GPIOParameters=GPIO_Label
PC12.GPIO_Label=HEATER
PC12.Signal=GPIO_Output
PC13.Mode=AlarmA_RoutedAF
PC13.Signal=RTC_OUT_ALARM
PC14-OSC32_IN\ (PC14).Mode=LSE-External-Oscillator
PC14-OSC32_IN\ (PC14).Signal=RCC_OSC32_IN
PC15-OSC32_OUT\ (PC15).Mode=LSE-External-Oscillator
PC15-OSC32_OUT\ (PC15).Signal=RCC_OSC32_OUT
PC3.GPIOParameters=GPIO_Label
PC3.GPIO_Label=FET_CUR-A2
PC3.Signal=SharedAnalog_PC3
PC4.GPIOParameters=GPIO_Label
PC4.GPIO_Label=Therm-spare1
PC4.Signal=ADCx_IN13
PC5.GPIOParameters=GPIO_Label
PC5.GPIO_Label=Therm-spare2
PC5.Signal=ADCx_IN14
PC8.GPIOParameters=GPIO_Label
PC8.GPIO_Label=DUMP_NOT
PC8.Signal=GPIO_Output
PD2.GPIOParameters=GPIO_Label
PD2.GPIO_Label=BQ_LD
PD2.Signal=GPIO_Output
PH0-OSC_IN\ (PH0).Mode=HSE-External-Oscillator
PH0-OSC_IN\ (PH0).Signal=RCC_OSC_IN
PH1-OSC_OUT\ (PH1).Mode=HSE-External-Oscillator
PH1-OSC_OUT\ (PH1).Signal=RCC_OSC_OUT
RCC.HSE_VALUE=8000000
RCC.SYSCLKFreq_VALUE=16000000
RCC.SYSCLKSource=RCC_SYSCLKSOURCE_PLLCLK
board=custom

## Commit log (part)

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2020-05-02 initial load with scad file
2020-05-05 update openscad work
2020-05-05 adding eagle files to be hacked
2020-06-24 start eagle bms layout work.
2020-06-24 add documentation directories
2020-07-01 updating files. work is on bmsR board pair
2020-07-06 save work on bmsbmsR and bmschgrR boards.
2020-07-07 save work and updates
2020-07-09 update and save work on bms boards
2020-07-11 save revisions and updates. Review still has not be done. Net, it is not ready.
2020-07-14 Fixed big time error on bmschgrR where discharge resistor not connected correctly for the internal discharge selection. Added pushbutton header on bmsbmsR.
2020-07-18 save eagle work on bmsbmsR and bmschgrR plus doc stuff
2020-07-22 save work on bmsbmsR bmschgrR and documentation
2020-07-23 save work on pcbs
2020-07-25 save work. Added on-board dump resistor to bmsbmsR
2020-11-23 add datasheet
2020-12-24 add new work on BQ76952 implementation
2020-12-28 backup work on bmsbmsBQ board sch and brd
2021-01-02 save work
2021-01-04 save work on bmsbmsBQ
2021-01-07 save layout work on bmsbmsBQ. First cut at layout completed, but tweaking and polygon arrangements needed. Schematic needs review. Current sensing and VBAT might be reconsidered.
2021-01-11 save and backup work on bmsbmsBQ
2021-01-17 changed CAN ISO1050 to ISO1042; added AM6G1215 isolated dc-dc converter option; text cleanups; AP7380-50Y for 5v regulators; LM7805T 5v regulator option
2021-01-26 save work on bmsbmsBQ. Updating not complete
2021-02-06 save and backup bmsbmsBQ design
2021-02-07 save work on bmsbmsBQ design. Revised CAN and I2C1 pins. Review and clean up still required
2021-02-11 renumbered fets and headers
2021-02-11 save and backup minor changes. working on renumber bmsbmsbq pcb
2021-02-11 bmsbmsbq renumbered using ulp from eagle 6.5
2021-02-12 minor adjustments to bmsbmsbq pcb
2021-02-13 save and backup bmsbmsbq board work. thermistor revision
2021-02-14 bmsbmsbq save and backup. 5v1 drives added i2c2 jic bus. 5v3 from bq reg2 drives 7400 for fet drive.
2021-02-20 update, save, backup
2021-02-20 save and backup latest work on bmsbmsBQ
2021-02-21 clean up silk screen layers on bmsbmsBQ
2021-03-01 small docx updates
2021-03-18 comments on docx and fix FET104 on bmsbmsBQ
2021-03-22 docx updates
2021-03-27 bmsbmsBQ updates.
2021-03-28 Remove D2 for 15v ORing in bmsbmsBQ
2021-04-01 update polarity PFET on bmsbmsBQ
2021-04-01 added missing gerber layer
2021-04-11 Changed thermistors from CHG, DSG to DCHG, DDSG. Added RC0/C100 in C0 line. Renamed solder pads
2021-04-25 minor changes to silk screen and updated Gerbers
2021-09-04 update work
2021-09-07 update and save work before starting spi to BQ chip additions, as well as uart monitoring. Current status is that the LEDs work OK.
2021-09-14 cell voltage, topstack, etc reading. Save work-in-progress.
2021-09-20 Discovered congif update multiple times was resetting things. BREG is now showing 6v+. thermistors working, but need calibration.
2021-09-21 save work.
2021-09-22 add readout of cell adc counts
2021-09-24 save and backup. cell balancing progress. bq fets appear to be about 23 ohms when ON
2021-09-24 add file
2021-10-04 save work. balancing in bq_items in progress.
2021-10-10 save and back work
2021-10-12 save work. 431R is sort of working. ALERT and ALARM 0x2 mask not cycling
2021-10-17 save and back eagle work
2021-10-20 bms1818 eagle routed w DRC OK. Begin updates learned from BQ board assembly. Save work before changes.
2021-10-22 save and backup work. Updating BQ eagle and 1818 eagle with items learned in first BQ pcb layout. Not all items complete.
2021-10-22 save 1818 and BQ pcb updates
2021-10-24 added opamp for current sense and pin #2 on ribbon header no longer a 2nd gnd
2021-10-24 cleaned up some erc errors and warnings
2021-10-26 add Adapt-BQto1818 eagle files
2021-10-26 add rj45-2x10 adaptor eagle files
2021-11-01 save work and backup
2021-11-08 Adding CAN routines and msgs. Save and backup. CAN debugging has not started.
2021-11-08 add missing files to git
2021-11-08 Add more missing files to repo
2021-11-08 Add more
2021-11-28 Replaced ISO1042 along with some minor sw changes to test for the gateway heartbeat msgs. Sedning receiving CAN msgs working.
2021-12-07 FanTask added and fan working
2021-12-17 First draft of maxbms14921 eagle layout
2021-12-18 standardized mounting holes, but BQ V2 not completed
2021-12-18 standardized holes on BQ-V2 board. 3.3v i2C headers had to be sacrificed
2021-12-23 Create LICENSE
2021-12-31 working on gerber
2022-01-04 update of pcbs. save work
2022-01-06 14921 pcb updates. DUMP 3 pin, plus VOred pin added
2022-01-08 mods to pcb 14921 to add 3.3 to 5v level shifters
2022-01-10 added voltage divider subboard
2022-01-10 save gerbering updates
2022-01-11 change 14921 pcb lettering to 1 mm
2022-01-11 14921 pcb outline revised to 10 mil
2022-01-11 still trying to outline to work with jclpcb.com
2022-01-12 bmsadapt18-16 pcb gerber work
2022-02-02 updated BQ with calibration and CAN msg readout
2022-02-03 Added heartbeat features to BQ #1 program
2022-02-21 add missing file
2022-02-25 save work on 14921 routine
2022-03-09 bmsmax14921 adcspi readadc beginning to work. Save work
2022-03-11 bmsmax14921 readbms work. switched to TIIM15 for bms delay timing
2022-03-15 Revised spi dma approach starting to work. Needs timing tests, etc.
2022-03-17 Major revision of bms readout. SPI interrupt no longer used. TIM15 and ADC interrupts drive sequence.
2022-03-18 bmsmax14921 revisions compiling and not falling into morse_traps. BMS chip still not installed
2022-03-23 bmsmax14921 save work. SPI changed to LSB first. cellbal.c and setting fets added
2022-04-05 bmsmax1421 getting good readings and discharge fets working. SMPL pin held low, notSMPL bit low during readout. Cycling EN pin not needed for good readings...I think.
2022-04-08 add missing files. something wrong with cell number 1 reading in this commit, but ok with older versions
2022-04-09 experimenting with walking discharge fets
2022-04-19 polynomial fitting for calibration
2022-04-20 save work on polynomial calibration
2022-04-27 thermistor calibration work save
2022-04-30 MISC ADC readout work
2022-05-07 save work for code working with cangateBMS command e
2022-05-11 save work on 14921 cell balancing
2022-05-14 save work for cangateBMS display
2022-06-02 add 1818 gerber zip
2022-06-12 save and backup work.
2022-06-30 bmsadbms1818 save and backup. Compiles. Not loaded or run.
2022-07-11 save and backup work on bmsbms1818
2022-07-13 save and backup 1818 work
2022-07-14 save and back 1818 work
2022-07-17 save and backup work on 1818
2022-07-19 save and backup work on 1818. working on exti4 end of conversion interrupts. as yet no joy
2022-07-20 save and backup
2022-07-21 save and backup 1818. Begin discharge FET code and testing
2022-07-25 save work. 1818 fan speed control added. cell 2 S pulldown resistor added to fix discharge problem. 1M only partial FET on, 100K solid on
2022-07-26 fixed fetonoff.c for backwards heater and dump on-off sense. Still checking out hw and sw
2022-08-01 save work. calibration of processor adcs in progress. internal temperature calculation not correct.
2022-08-01 fixed internal temp computation. 3.3v Vcc and CAL1,2 is based on Vcc 3.0 in datasheet footnote.
2022-08-02 fixed fan tach. PB10 now uses EXTI15_10 interrupts. Discovered thermistor readings jump when temp gets to about 33 degC. Requires reset to get readings normal.
2022-08-02 add missing BMSTask
2022-08-02 add missing rtcregs
2022-08-03 changes to bmsspi.c for TIMSTATE_1 may have corrected the rare timeout trap.
2022-08-06 Started additions to CanCommTask to send requests to BMSTask.
2022-08-09 save work. Working on cell balancing which is not working
2022-08-16 begin bmsbms1818-v2 pcb
2022-08-17 bmsbms1818-v2 update. Renumbered top and bottom. Swapped top and bottom for the two CC caps so that the top are all resistors and the bottom all caps.
2022-08-18 save work on eagle files for 1818-v2. Renumbered, SDO via added. GPIO assignments NOT changed.
2022-09-04 CRC additional to flashing added to scripts, .s and .ld files
2022-09-08 scripts modified to work with CANloader for checksum and crc
2022-09-15 reset cmd fixed in CanCommTask
2022-10-02 add cc script for compile and flash over CAN
2022-10-15 save latest updates to bmsadbms1818-v2 pcb
2022-10-17 save updates. boards 2 and 3 ok
2022-10-22 save work. checking balancing.
2022-10-23 changed divider for HV comparator
2022-10-25 update eagle files and gerber zips added
2022-11-03 update script-all
2022-11-05 some RTC carry over cleanup
2022-11-27 Add pcb header description for 1818
2022-12-17 bms-Adapt-DE9to2x5 sub-board eagle file update
2022-12-17 bms sub-board ready and gerber checked
2022-12-27 update docs
2023-01-05 BMS using loader CAN id for responses. Significant changes.
2023-01-05 script added
2023-01-06 B0E0parms
2023-01-08 rtc save restore fixed. chg and balancing work in progress
2023-01-10 changes to main and bq_items for charging and balancing logic
2023-01-13 BMS 1818 updated for DUMP2 not cycling with on-board charger
2023-01-23 some cleanup of main and CanCommTask ect.
2023-01-24 More debugging and testing of BMS1818 and cangateBMS
2023-01-30 added openscad file
2023-02-25 add files for proxy pack pcb and 3D frame
2023-03-11 charger parameter tweaking
2023-03-23 Add bms1818 eagle files with correction of 8 pin CAN driver rx/tx in earlier versions. > Eliminate no external discharge fet option with 3 pin resistor configuration and added SMD discharge resistor 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
2023-05-17 update check
2023-05-27 added charger hysteresis connection
2023-07-01 update B0E00000 for chgr v module voltage params
2023-07-07 Change to keep chrgr on after cell trips max and discharge to max - delta while other cells are coming up
2023-07-07 paramet update
2023-07-18 many small changes and minicomfilter program added
2023-07-23 updates chasing bmsspi bug
2023-07-25 updates for chasing bogus readings bug
2023-08-01 added bridgemissing routine
2023-08-07 Many timer changes and BMS request added ADC rate code. More testing is needed, but seems-to-work. Further experiments with EXTI to detect end of ADC conversion still shows SDO lines does not go high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
2023-08-09 removed some test lines from main.
2023-08-17 save current work on polling provisions
2023-08-20 backup work
2023-08-21 save and backup.
2023-08-25 cangateBMS command e and associated 1818 program for setting discharge fets. needs more testing
2023-08-27 save current work with cangateBMS
2023-09-01 save and backup. cangateBMS work
2023-09-13 fixed saving restoring charge-discharge mode problem where CAN msg command 31 made it look like it had received a command to go into charge mode
2023-09-16 mklist1,2 for generating .cc file for loading programs over CAN for BMS nodes
2023-10-07 save and backup. working with cangateBMS E command
2024-07-06 added -e option to bin/bash scripts for .cc sequence so as to bombout on any script error.
2024-07-12 fanop.c algorithm work. Set for original
2024-07-16 fixed ccall-list script to stop after making list
2024-07-17 update and push
2024-07-21 loading over CAN work
2024-09-04 Update params for current sense damaged units
2024-09-16 added SWDIO pullup and NRST single pin header to v3
2024-09-25 morse_trap 91 enabled. RTC regs have counter.
2025-04-08 update cc for hack
2025-04-22 update params for ELCON charging for GSMs modules
2025-11-09 add eagle to kicad converted files
2026-02-12 Fix module volts scaling that had divisor of 1000 instead of 100 for gsm boards
2026-02-17 add ccskipmm to skip compile
2026-02-24 ccallx script added
2026-03-30 Fixed dump timeout.
2026-05-17 Add sum of cell voltages to MISCQ list, and update cangateBMS e command to retrieve and print it
